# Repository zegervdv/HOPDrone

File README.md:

HOPDrone
========

Indoor localization for drones

## Code

For Least Mean Square implementation: checkout `code-lms`.

For Kalman implementation: checkout `code-kalman`.

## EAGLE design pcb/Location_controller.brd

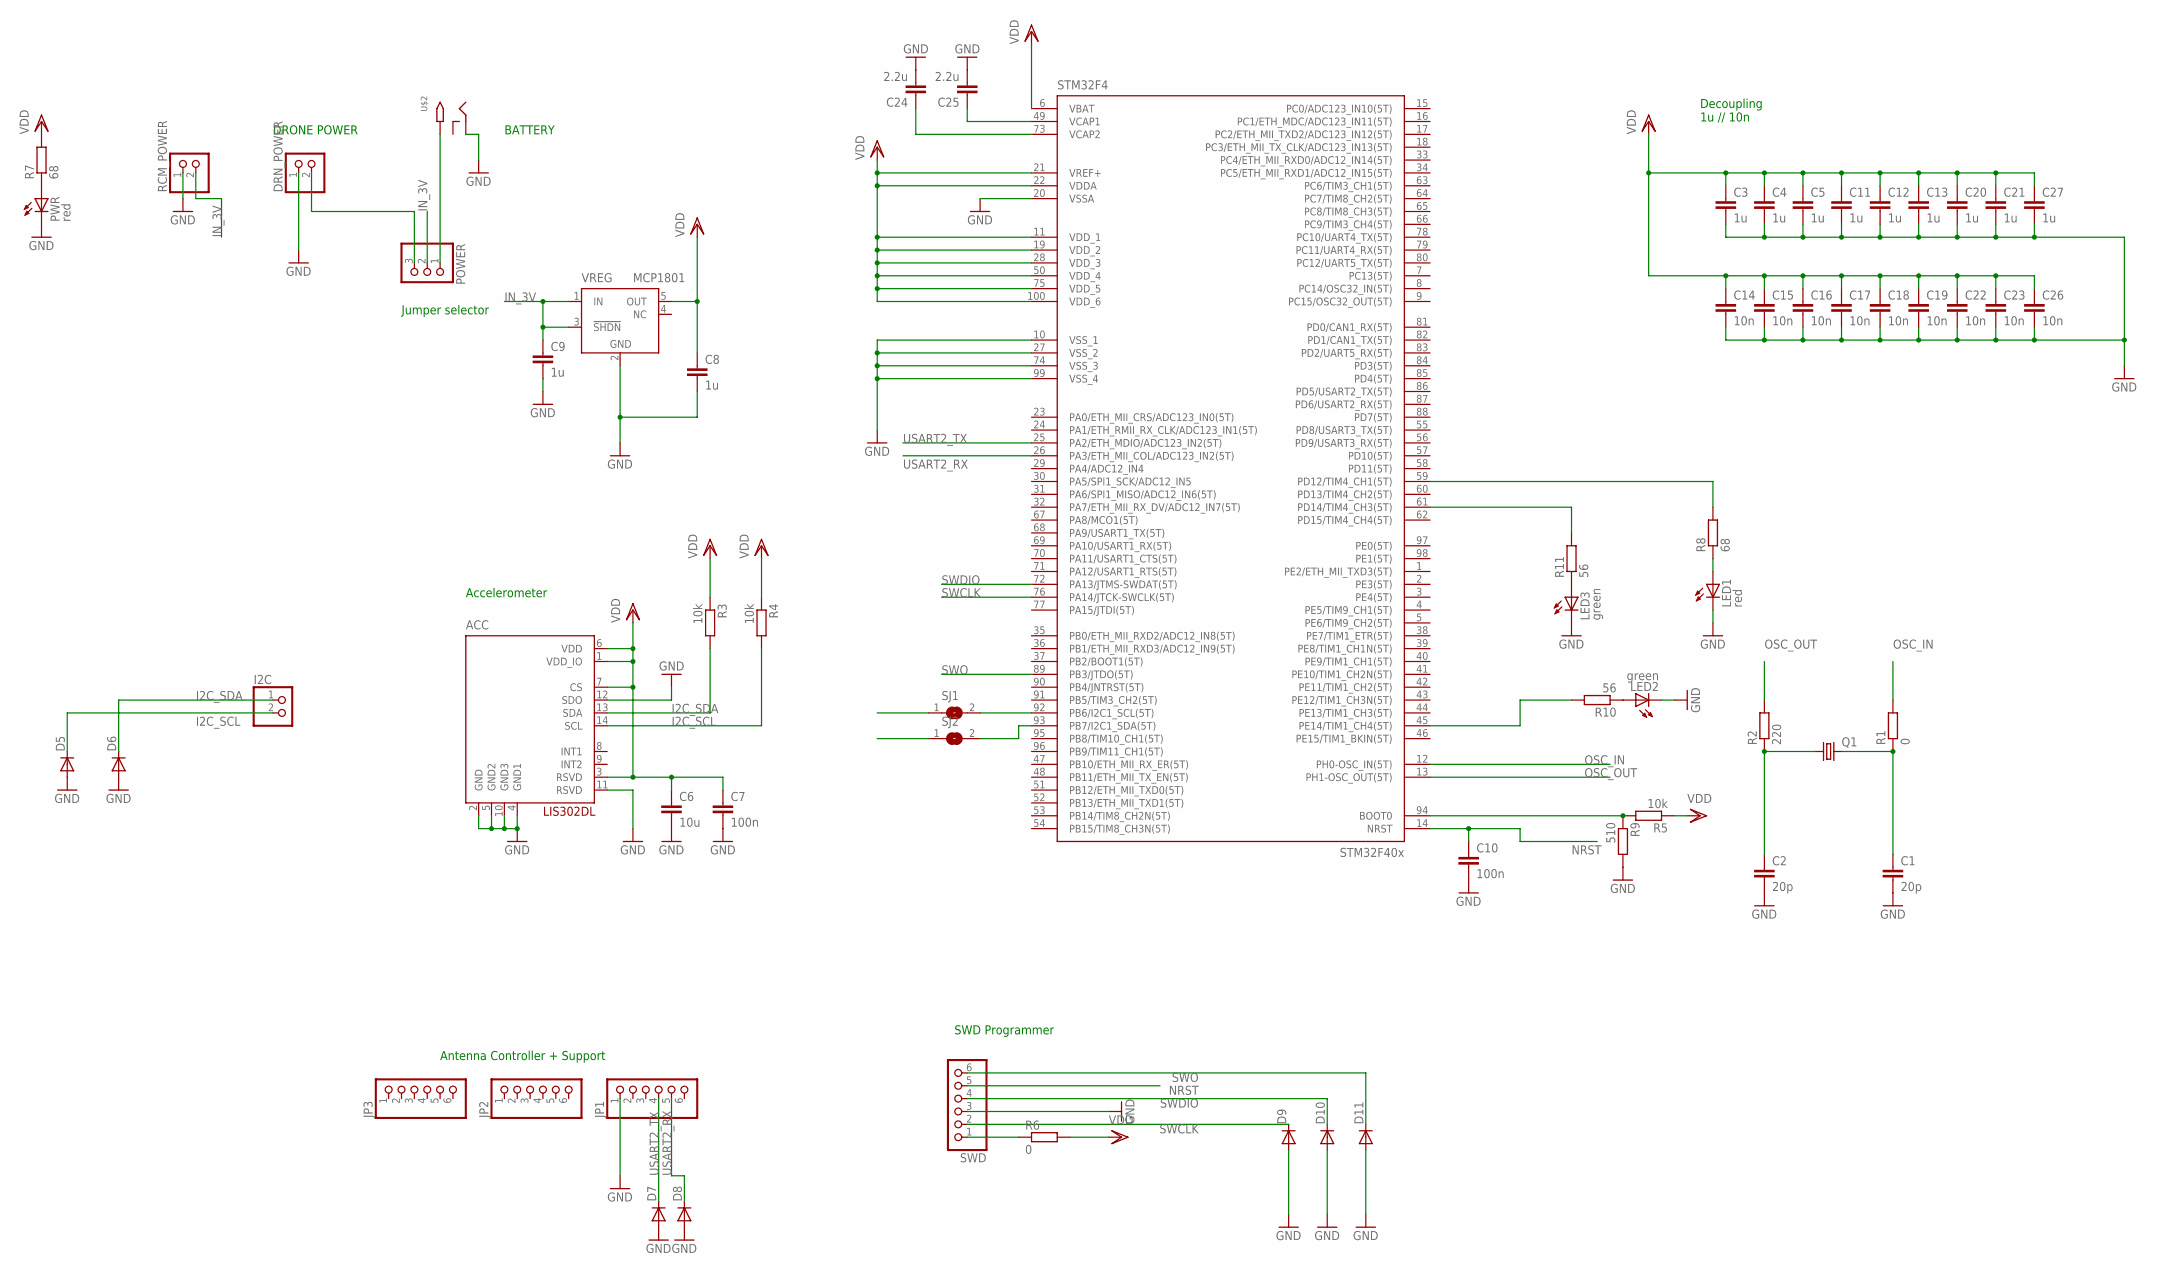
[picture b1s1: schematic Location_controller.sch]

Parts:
ACC: LIS302DL; LGA-14
C1, C2: 20p; C0805
C3, C4, C5, C8, C9, C11, C12, C13, C20, C21, C27: 1u; C0805
C6: 10u; C0805
C7, C10: 100n; C0805
C14, C15, C16, C17, C18, C19, C22, C23, C26: 10n; C0805
C24, C25: 2.2u; C0805
D5, D6, D7, D8, D9, D10, D11: DIODE-SOD523; SOD523
DRN_POWER: PINHD-1X2; 1X02
I2C: PINHD-1X2; 1X02
JP1, JP2, JP3: PINHD-1X6; 1X06
LED1: red; CHIPLED_0805
LED2, LED3: green; CHIPLED_0805
POWER: PINHD-1X3; 1X03
PWR: red; CHIPLED_0805
Q1: CRYSTALHC49S; HC49/S
R1, R6: 0; R0805
R2: 220; R0805
R3, R4, R5: 10k; R0805
R7, R8: 68; R0805
R9: 510; R0805
R10, R11: 56; R0805
RCM_POWER: PINHD-1X2; 1X02
SJ1, SJ2: SJ
STM32F4: STM32F407V; TQFP100
SWD: PINHD-1X6; 1X06
U$2: 2.1MMJACKTHM; PJ-102A
VREG: MCP1801; SOT23-5

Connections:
GND: ACC.2 (GND), ACC.4 (GND1), ACC.5 (GND2), ACC.10 (GND3), ACC.11 (RSVD), ACC.12 (SDO), C1.2, C2.2, C3.2, C4.2, C5.2, C6.2, C7.2, C8.2, C9.2, C10.2, C11.2, C12.2, C13.2, C14.2, C15.2, C16.2, C17.2, C18.2, C19.2, C20.2, C21.2, C22.2, C23.2, C24.2, C25.2, C26.2, C27.2, D5.A, D6.A, D7.A, D8.A, D9.A, D10.A, D11.A, DRN_POWER.1, JP1.1, LED1.C, LED2.C, LED3.C, PWR.C, R9.2, RCM_POWER.1, STM32F4.10 (VSS_1), STM32F4.20 (VSSA), STM32F4.27 (VSS_2), STM32F4.74 (VSS_3), STM32F4.99 (VSS_4), SWD.3, U$2.RING, VREG.2 (GND)
I2C_SCL: ACC.14 (SCL), D5.C, I2C.2, R4.2, SJ1.1
I2C_SDA: ACC.13 (SDA), D6.C, I2C.1, R3.2, SJ2.1
IN_3V: C9.1, POWER.2, RCM_POWER.2, VREG.1 (IN), VREG.3 (!SHDN)
unnamed: C2.1, Q1.1, R2.1
unnamed: C1.1, Q1.2, R1.1
unnamed: R5.2, R9.1, STM32F4.94 (BOOT0)
unnamed: DRN_POWER.2, POWER.3
unnamed: POWER.1, U$2.TIP
unnamed: R6.1, SWD.1
unnamed: C25.1, STM32F4.49 (VCAP1)
unnamed: C24.1, STM32F4.73 (VCAP2)
unnamed: PWR.A, R7.1
unnamed: LED1.A, R8.1
unnamed: R8.2, STM32F4.59 (PD12/TIM4_CH1(5T))
unnamed: LED2.A, R10.1
unnamed: R10.2, STM32F4.45 (PE14/TIM1_CH4(5T))
unnamed: LED3.A, R11.1
unnamed: SJ2.2, STM32F4.93 (PB7/I2C1_SDA(5T))
unnamed: R11.2, STM32F4.61 (PD14/TIM4_CH3(5T))
unnamed: SJ1.2, STM32F4.92 (PB6/I2C1_SCL(5T))
NRST: C10.1, STM32F4.14 (NRST), SWD.5
OSC_IN: R1.2, STM32F4.12 (PH0-OSC_IN(5T))
OSC_OUT: R2.2, STM32F4.13 (PH1-OSC_OUT(5T))
SWCLK: D9.C, STM32F4.76 (PA14/JTCK-SWCLK(5T)), SWD.2
SWDIO: D10.C, STM32F4.72 (PA13/JTMS-SWDAT(5T)), SWD.4
SWO: D11.C, STM32F4.89 (PB3/JTDO(5T)), SWD.6
USART2_RX: D8.C, JP1.5, STM32F4.26 (PA3/ETH_MII_COL/ADC123_IN2(5T))
USART2_TX: D7.C, JP1.4, STM32F4.25 (PA2/ETH_MDIO/ADC123_IN2(5T))
VDD: ACC.1 (VDD_IO), ACC.3 (RSVD), ACC.6 (VDD), ACC.7 (CS), C3.1, C4.1, C5.1, C6.1, C7.1, C8.1, C11.1, C12.1, C13.1, C14.1, C15.1, C16.1, C17.1, C18.1, C19.1, C20.1, C21.1, C22.1, C23.1, C26.1, C27.1, R3.1, R4.1, R5.1, R6.2, R7.2, STM32F4.6 (VBAT), STM32F4.11 (VDD_1), STM32F4.19 (VDD_2), STM32F4.21 (VREF+), STM32F4.22 (VDDA), STM32F4.28 (VDD_3), STM32F4.50 (VDD_4), STM32F4.75 (VDD_5), STM32F4.100 (VDD_6), VREG.5 (OUT)

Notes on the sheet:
Decoupling 1u // 10n
Accelerometer
Jumper selector
Antenna Controller + Support
SWD Programmer
BATTERY
DRONE POWER

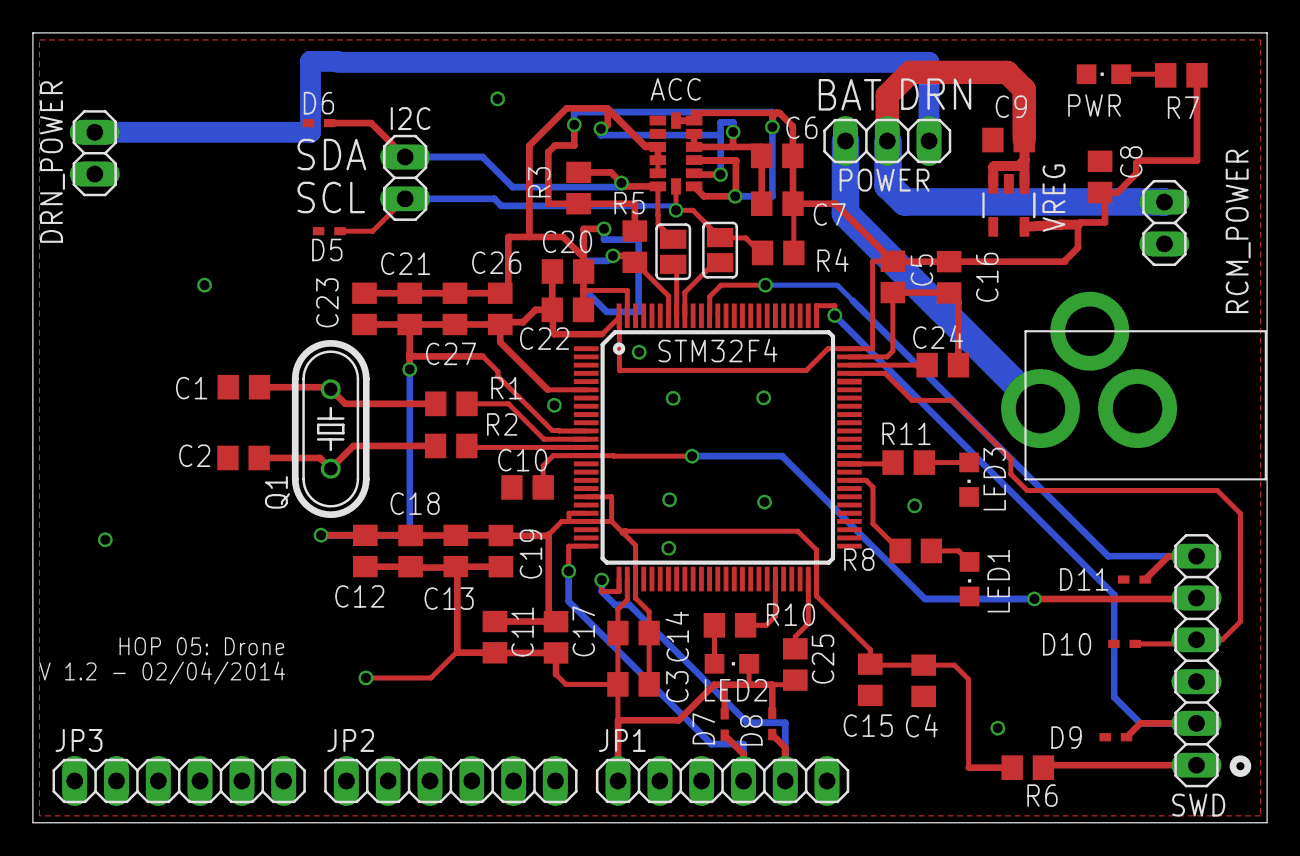
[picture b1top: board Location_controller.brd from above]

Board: 2 copper layers, 75.0 x 48.0 mm, 64 parts (1 on the bottom side), 30 nets.

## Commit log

2014-02-20 Add least mean squares matlab simulation
2014-02-20 Added calculation of procentual error
2014-02-20 Calculates average error
    Average error for different values of error on distance measurement
2014-02-20 Setup basic report
2014-02-20 Initial setup of libraries with LED_blink demo
2014-02-20 Remove pdf from repo
2014-02-22 Add PCB schematic/layout
2014-02-22 Add crystal to layout
2014-02-26 Report: LMS algorithm
2014-02-26 Add Voltage Regulator and application circuits
2014-02-26 Add Accelerometer to PCB
2014-02-26 Add Gyroscope to PCB
2014-02-27 Add SWD programmer description
2014-02-27 Add pin header
2014-02-27 typos corrected
    part LMS method
2014-02-27 rewriting sum
    sum(vector')' => sum(vector,2)
2014-02-27 UKF
    unscented kalman filter v1.0
2014-02-27 Move Unscented Kalman Filter to matlab script
    renames "matlab/Unscented Kalman Filter" to "matlab/Unscented_Kalman_Filter.m"
2014-03-01 Add virtual machine
2014-03-05 Part one of Kalman Filter
2014-03-06 Update Unscented_Kalman_Filter.m
    Part two
2014-03-06 problem cholesky decomposition fixed
2014-03-08 Add decoupling to schematic + initial layout
2014-03-09 Add connections to RCM
2014-03-09 Add SWD programmer connectors
2014-03-09 Improve ignores
2014-03-11 Add more layering
2014-03-11 Further pcb layout routing
2014-03-11 Remove positive definite fix
2014-03-11 Update UKF to add noise to measurements
2014-03-11 Add barrel DC-jack to pcb
2014-03-12 Finish pcb routing
2014-03-12 Silk-screening for pcb
2014-03-12 Add PWR and ERR indicator LEDs
2014-03-14 Add I2C debug pins
2014-03-15 Add LED error indicator function
2014-03-16 Automatically attach USB device in Vagrant
2014-03-17 Add Zener Diodes to I2C pins
2014-03-17 Add resistor to GND at BOOT0
2014-03-17 Increase thickness on powerlines
2014-03-17 added zener to SWDIO EN SWO
2014-03-17 Change silkscreening for Programmer
2014-03-17 Additional broadening of powerlines
2014-03-17 Add TVS for I2C and USART connections
2014-03-19 Add ground plane
2014-03-19 Add ground plane on top
2014-03-19 Add antenna measurements
2014-03-19 Move crystal closer to microcontroller
2014-03-19 Add TVS to programmer pins
2014-03-21 Swap power plug for correct dimensions
2014-03-21 Move powerpins
2014-03-23 Move RCM_POWER pins to correct position
2014-03-23 Add Bill of Materials
2014-03-23 Swap voltage regulator for one in stock
2014-03-24 Other crystal
2014-03-24 Connectors Farnell
2014-03-26 Fix error in varh
    varh was calculated as (1x4) x (4x1) yielding a constant in all positions
    now varh is symmetric and positive definite
2014-03-26 Finish Kalman and compare measurements
2014-03-26 Fix Kalman filter
2014-03-26 Extend Kalman filter with accelerometer predictions
2014-03-26 Add predictions and measurement updates for accelerometer
    The accelerometer data is added to the measurement update and the sigmapoints
    are used to predict the acceleration.
2014-03-27 Add conditional to enable accelerometer
2014-03-27 more detailed cdf
2014-03-27 add sample frequency as parameter
2014-03-27 fix accelerometer measurement update
2014-03-27 Move powerpins to final location
2014-03-27 Add first presentation template
2014-03-31 Presentation: Inleiding en Algoritmes
2014-03-31 Presentation: Antenna reference and design path
2014-03-31 Add data files from ADS simulation + parse
2014-03-31 Add eps of simulation data
2014-03-31 Add images to presentation
2014-03-31 Add simulations to presentation
2014-04-01 Add pdf images for presentation
2014-04-01 Presentation: Antenna finished
2014-04-01 Add table of contents as final slide
2014-04-01 Split table of contents in two columns
2014-04-01 Typo
2014-04-01 Typo bis
2014-04-02 Add additional LEDS to board
    See pcb/leds.md for pin mapping
2014-04-03 Create patch_stairs_v2
2014-04-03 Add script to compare S22 measurements
2014-04-03 Add updated measurements
2014-04-03 Add measurements patch stairs 2
2014-04-03 Add new S11 measurements
    More accurate measurements by using ferrites
    Version 2 is original, unadjusted version
2014-04-03 Fix pcb remarks
    - Swap C4-C15 and C3-C14
    - Add vias under chip
    - Reroute trace under power jack
2014-04-03 Disconnect SDO pin on accelerometer
2014-04-03 Reorganise measurement and simulation data
2014-04-03 Add Farnell basket
2014-04-04 Add solder bridges to disconnect accelerometer
2014-04-04 Update basket
2014-04-04 Add titles to antenna_comparison
2014-04-07 Change Libraries
    Add official libraries in separate folder
2014-04-07 Add software LED drivers
2014-04-07 Compile MatrixFunctions into build
2014-04-07 Let make only recompile changed files
2014-04-07 Clean Libraries
2014-04-07 Rename flash_error() to generic LED_blink()
2014-04-07 Move initialization code to system.c
2014-04-09 Initial interface for Kalman
2014-04-12 Optimize unscented_kalman_filter by reformatting sigmapoints
2014-04-12 Optimize unscented_kalman_filter for mu
    Use transpose rules to reduce transpositions
2014-04-12 Optimize unscented_kalman_filter by reformatting anch
2014-04-12 Don't compile Q15 and Q31 matrix libs
2014-04-12 Add Cholesky decomposition algorithm
2014-04-13 Change cholesky_decomp to use pointers
2014-04-14 Add initialize function for weight factors
2014-04-14 Add initialization for position and sigmapoints
2014-04-14 Initialize F and G matrix for Kalman
2014-04-14 Initializer for dimensional matrices
2014-04-14 Add initializers for variance matrices
2014-04-14 Add kalman prediction step
2014-04-14 Test functions with LEDs
2014-04-14 Arrays have to be created in main
2014-04-21 Report: Antenna Topology and Design
    Added paragraph on antenna topologies and design. TODO: Add optimized
    dimensions of patch in a table at end of paragraph. TODO: Paragraphs on
    simulation results and measurements anechoic chamber.
2014-04-24 Add source files to communicate with RCM over UART
2014-04-24 Initialize and check USART connection to RCM
2014-04-24 Complete RCM initialization
2014-04-26 Initialize USART connection only once
2014-04-26 Add Range request code
2014-04-27 Clean up code for ranging and rcm communication
2014-04-27 Add 2D-LMS code
2014-04-27 Calculate roots in update_sigmapoints
2014-04-27 Finish update_sigmapoints
2014-04-27 Return estimated position to rcm
2014-04-28 Report: Started section Antenna Simulation
2014-04-28 Add flags to choose mode
2014-04-28 Add anchors and update positions and measurements
2014-04-28 3D LMS algoritme implemented
2014-04-28 Missing semicolon in lms.h and bracket in lms.c
2014-04-28 Add getIntersections3D to LMS
2014-04-28 Add Kalman measurement update up to calculation of cov
2014-04-28 Complete measurement update
2014-04-28 Perform update in main loop
2014-04-28 3D LMS finished
2014-04-28 Add small section about PCB
2014-04-28 Add accelerometer interface
2014-04-28 Add I2C read/write functions for accelerometer
2014-04-28 Initialize accelerometer control register
2014-04-29 Error corrected: return value get3DIntersections
2014-04-29 Include lms.h in main.c
2014-04-29 Cleaned up code and added comments
2014-04-29 Figures in English
2014-04-29 Add accelerometer data to DoLoc struct
2014-04-29 Remove non-existing file Makefile
2014-05-02 Add Additional Compiler flags
2014-05-02 corrections LMS - address matrix correctly
2014-05-03 Fix typo in readme
2014-05-03 Fix communication errors
    Add interrupt handlers to enable communication with RCM host
2014-05-03 Remove 3D code from master
2014-05-03 Fix typos in report
2014-05-03 Improve section about PCB design
2014-05-03 Add read function to accelerometer
2014-05-04 Use uint8_t for accelerometer data
2014-05-04 Use auto increment to read accelerometer faster
2014-05-05 report
    add figures + correct references
2014-05-05 Matlab implementation of LMS
2014-05-05 add figure + correct typos
2014-05-05 Finished antenne section report
2014-05-06 write introduction
2014-05-06 Fix initializations of matrices
2014-05-06 Kalman filter : start section Kalman
2014-05-06 add simulation results
2014-05-06 Send accelerometer data in rcm packets
2014-05-06 Fix typo in defines of the accelerometer
2014-05-06 Fix conversion with accelerometer data
2014-05-07 add cast to float32_t * for arrays
2014-05-07 update matlab figures + finish section algorithms
2014-05-07 Solve LMS algoritme problems
2014-05-07 Fix reuse of matrices and test for nans
2014-05-07 Corrections to Antenna part of report
2014-05-07 Proof reading the report
2014-05-08 report correct up to simulations antenna
2014-05-08 report correct typos
2014-05-08 Fix some bad initialisations
2014-05-08 Add radiation pattern parsing scripts
2014-05-08 Add Roll to Antenna measurement at 4.5GHz
2014-05-08 Add image of assembled PCB to report
2014-05-08 Imporve figure of antenne comparison
2014-05-08 Larger Simulation images
2014-05-08 Fix bug in parser script
2014-05-08 Add presentation 2, using 1 as base
2014-05-08 Added radpats to report, section antenna
2014-05-08 Add slide numbers
2014-05-08 Improve title page
2014-05-09 Finish up report
2014-05-09 some typos corrected
2014-05-09 Discuss full ground plane in section PCB
2014-05-12 Use different Cholesky factorization algorithm
2014-05-12 add Los figure
2014-05-12 Started antenne section presentation 2
2014-05-12 varia
2014-05-12 Finished antenna part presentation
2014-05-12 Add section Besluit to presentation
2014-05-12 add section microcontroller + algorithms to presentation
2014-05-12 Add section Besluit to presentation_2
2014-05-12 Small layout corrections microcontroller
2014-05-12 Fix errors in kalman
2014-05-12 Use node 104
2014-05-12 Change accelerometer sensitivity to 2.3g
2014-05-12 Fix error in data transfer with GUI
2014-05-13 Clean up code
2014-05-13 Add small schematic to explain ESD
2014-05-13 Small update to presentation
2014-05-13 Fix error with image names in report
2014-05-14 Vernederlandsen van presentatie
2014-05-14 Correct title presentation
